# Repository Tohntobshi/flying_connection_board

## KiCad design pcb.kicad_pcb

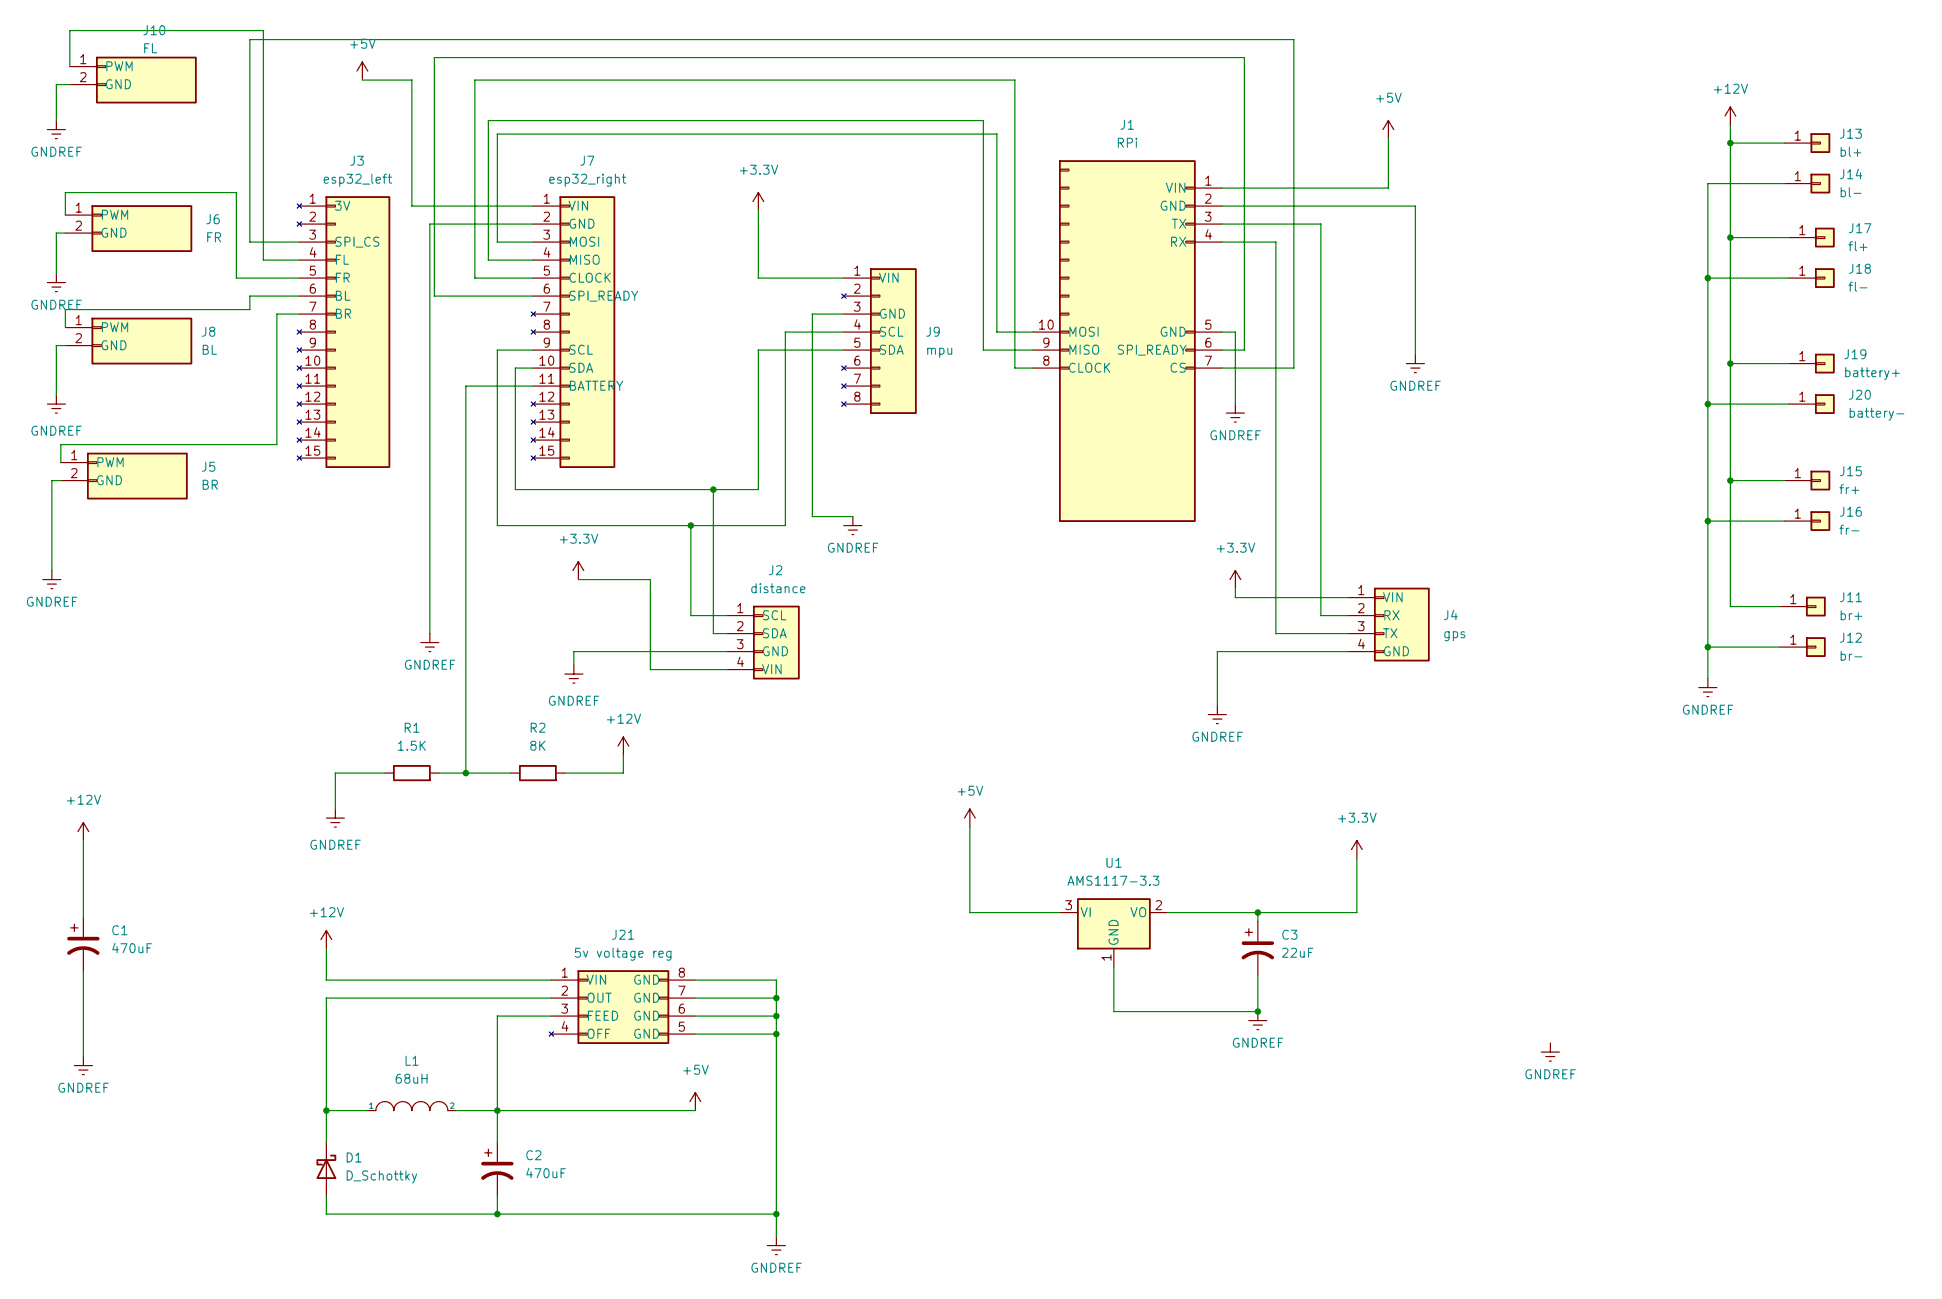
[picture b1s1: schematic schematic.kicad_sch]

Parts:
C1, C2: 470uF; CP_Radial_D10.0mm_P5.00mm
C3: 22uF; CP_Radial_D5.0mm_P2.00mm
D1: D_Schottky; D_2010_5025Metric_Pad1.52x2.65mm_HandSolder
J1: RPi; my_rpi_pins
J2: distance; PinSocket_1x04_P2.54mm_Vertical
J3: esp32_left; PinSocket_1x15_P2.54mm_Vertical
J4: gps; PinSocket_1x04_P2.54mm_Vertical
J5: BR; PinSocket_1x02_P2.54mm_Vertical
J6: FR; PinSocket_1x02_P2.54mm_Vertical
J7: esp32_right; PinSocket_1x15_P2.54mm_Vertical
J8: BL; PinSocket_1x02_P2.54mm_Vertical
J9: mpu; PinSocket_1x08_P2.54mm_Vertical
J10: FL; PinSocket_1x02_P2.54mm_Vertical
J11: br+; power_connector
J12: br-; power_connector
J13: bl+; power_connector
J14: bl-; power_connector
J15: fr+; power_connector
J16: fr-; power_connector
J17: fl+; power_connector
J18: fl-; power_connector
J19: battery+; power_connector
J20: battery-; power_connector
J21: 5v voltage reg; SO-8_3.9x4.9mm_P1.27mm
L1: 68uH; L_12x12mm_H8mm
R1: 1.5K; R_Axial_DIN0207_L6.3mm_D2.5mm_P7.62mm_Horizontal
R2: 8K; R_Axial_DIN0207_L6.3mm_D2.5mm_P7.62mm_Horizontal
U1: AMS1117-3.3; SOT-223-3_TabPin2

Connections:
+3V3: C3.1, J2.4 (VIN), J4.1 (VIN), J9.1 (VIN), U1.2 (VO)
+5V: C2.1, J1.1 (VIN), J7.1 (VIN), J21.3 (FEED), L1.2, U1.3 (VI)
+12V: C1.1, J11.1, J13.1, J15.1, J17.1, J19.1, J21.1 (VIN), R2.2
GNDREF: C1.2, C2.2, C3.2, D1.2 (A), J1.2 (GND), J1.5 (GND), J2.3 (GND), J4.4 (GND), J5.2 (GND), J6.2 (GND), J7.2 (GND), J8.2 (GND), J9.3 (GND), J10.2 (GND), J12.1, J14.1, J16.1, J18.1, J20.1, J21.5 (GND), J21.6 (GND), J21.7 (GND), J21.8 (GND), R1.1, U1.1 (GND)
unnamed: D1.1 (K), J21.2 (OUT), L1.1
unnamed: J1.3 (TX), J4.2 (RX)
unnamed: J1.4 (RX), J4.3 (TX)
unnamed: J1.6 (SPI_READY), J7.6 (SPI_READY)
unnamed: J1.7 (CS), J3.3 (SPI_CS)
unnamed: J1.8 (CLOCK), J7.5 (CLOCK)
unnamed: J1.9 (MISO), J7.4 (MISO)
unnamed: J1.10 (MOSI), J7.3 (MOSI)
unnamed: J2.1 (SCL), J7.9 (SCL), J9.4 (SCL)
unnamed: J2.2 (SDA), J7.10 (SDA), J9.5 (SDA)
unnamed: J3.5 (FR), J6.1 (PWM)
unnamed: J3.6 (BL), J8.1 (PWM)
unnamed: J3.7 (BR), J5.1 (PWM)
unnamed: J7.11 (BATTERY), R1.2, R2.1
unnamed: J3.4 (FL), J10.1 (PWM)

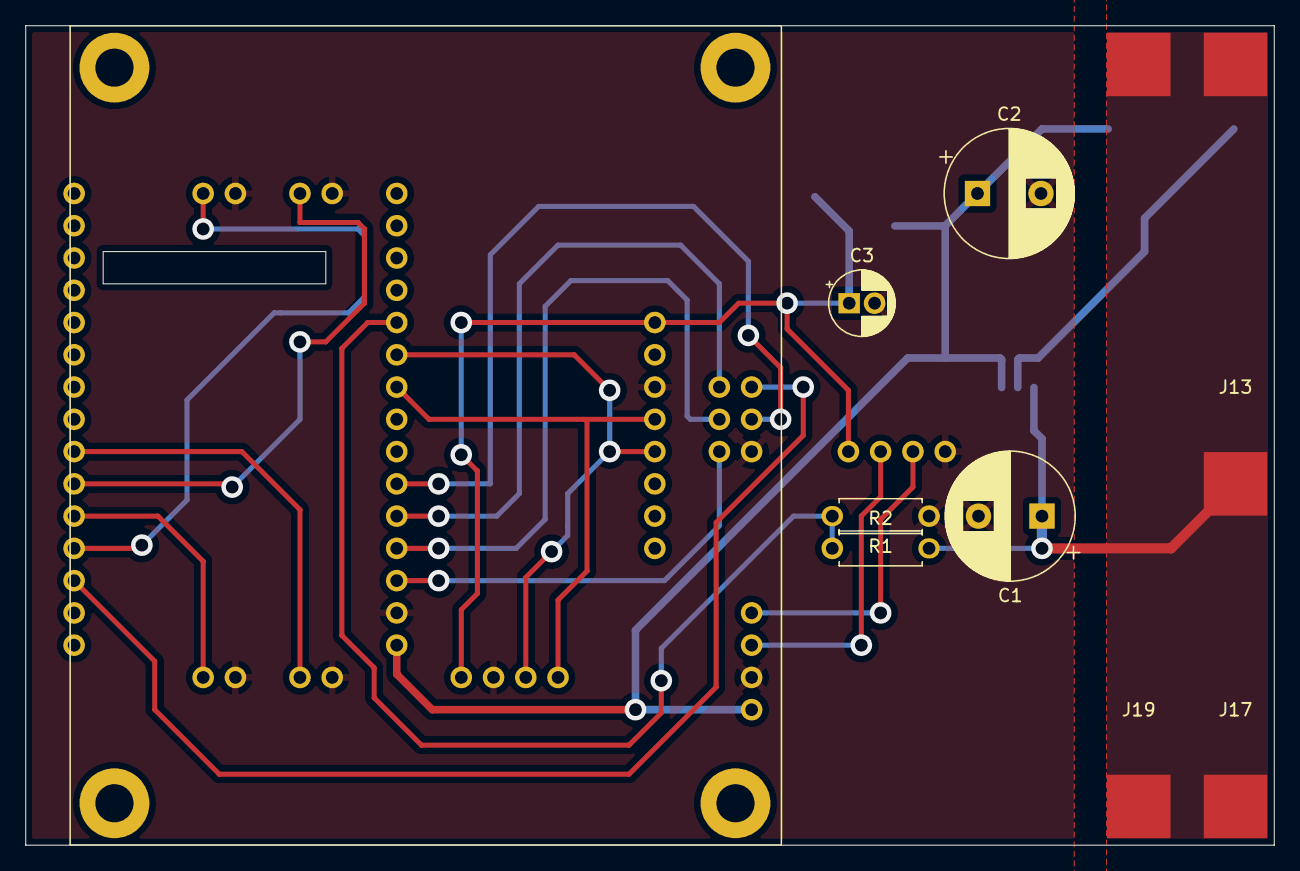
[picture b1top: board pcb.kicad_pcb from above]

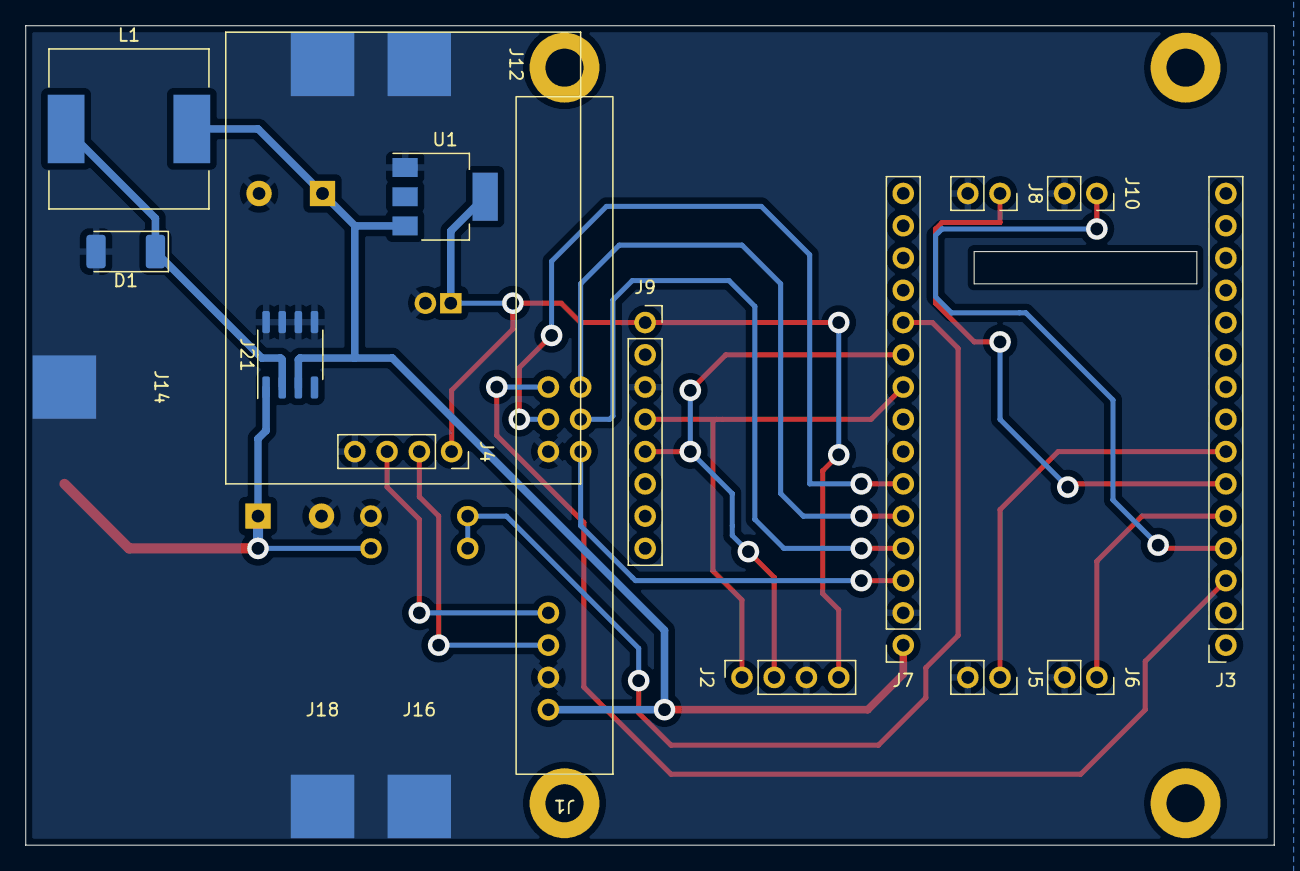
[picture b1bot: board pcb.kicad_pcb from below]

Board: 2 copper layers, 98.3 x 64.5 mm, 29 parts (19 on the bottom side), 19 nets.
